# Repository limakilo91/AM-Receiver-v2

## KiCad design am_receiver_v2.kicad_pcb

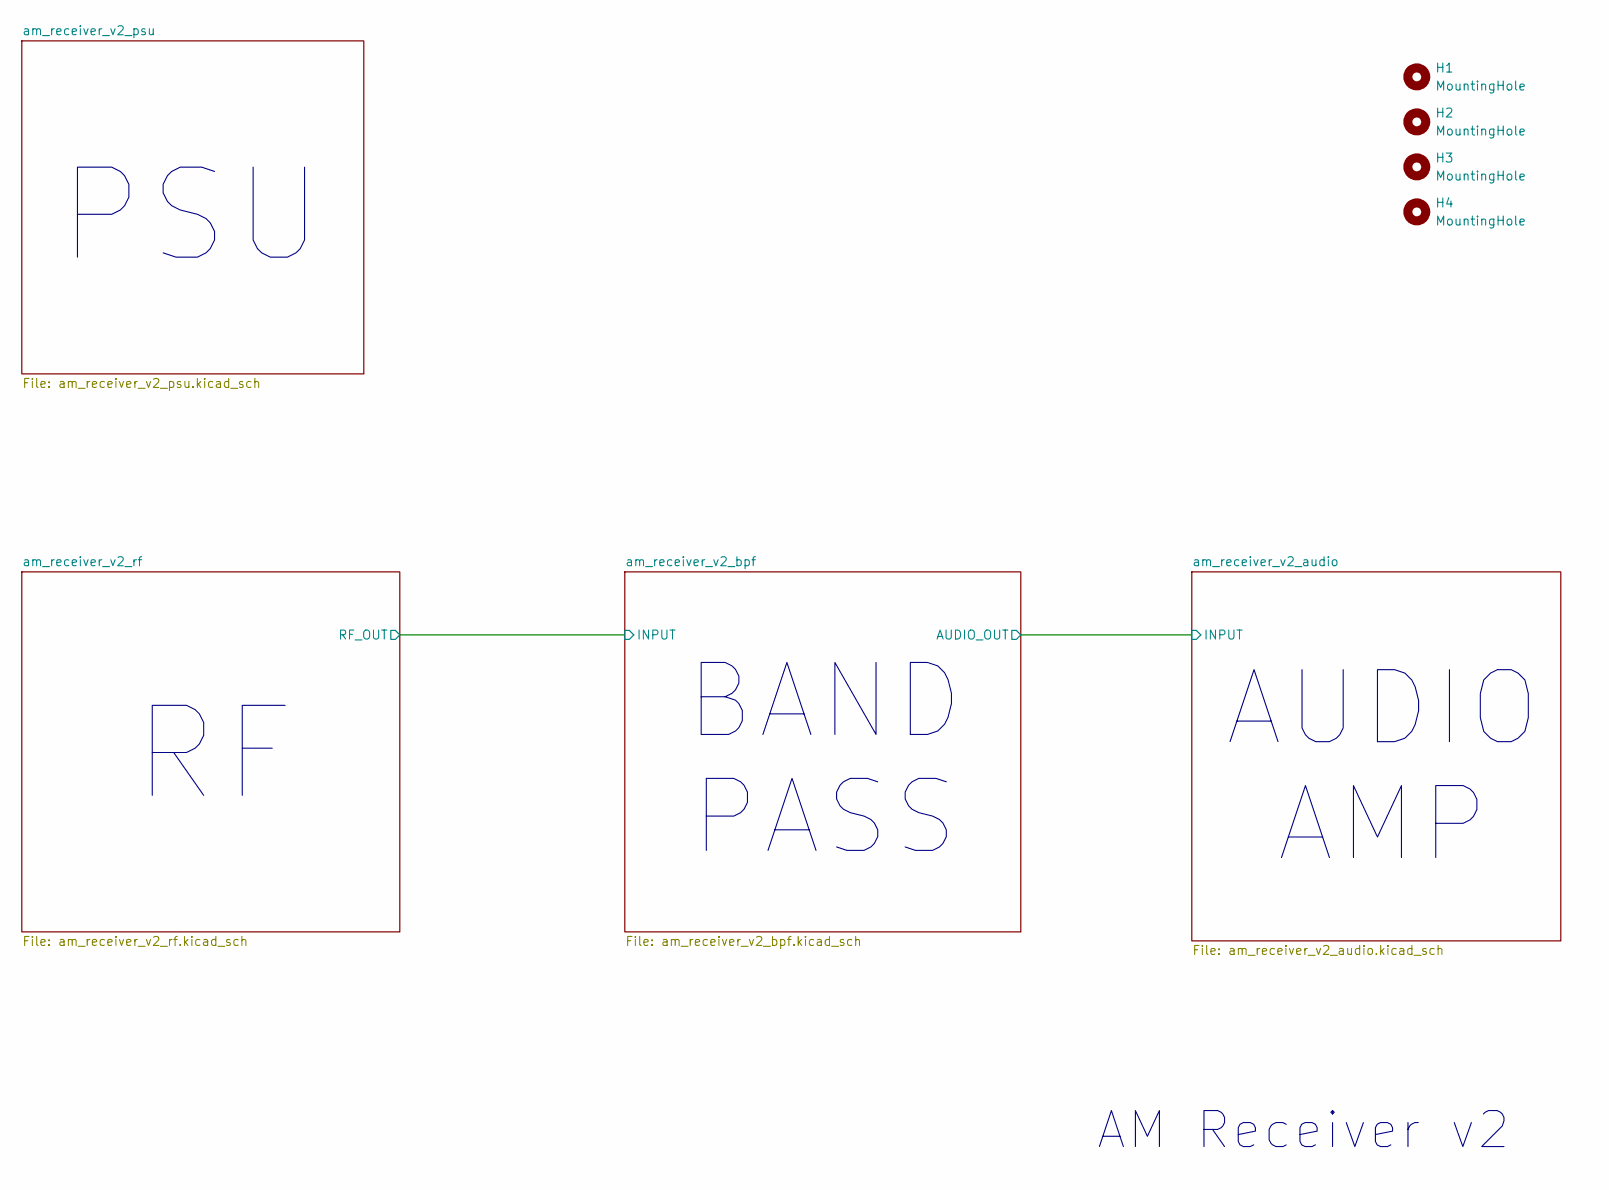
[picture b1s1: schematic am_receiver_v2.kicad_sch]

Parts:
H1, H2, H3, H4: MountingHole; MountingHole_3.2mm_M3_DIN965

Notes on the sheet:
PSU
AUDIO AMP
AM Receiver v2
BAND PASS

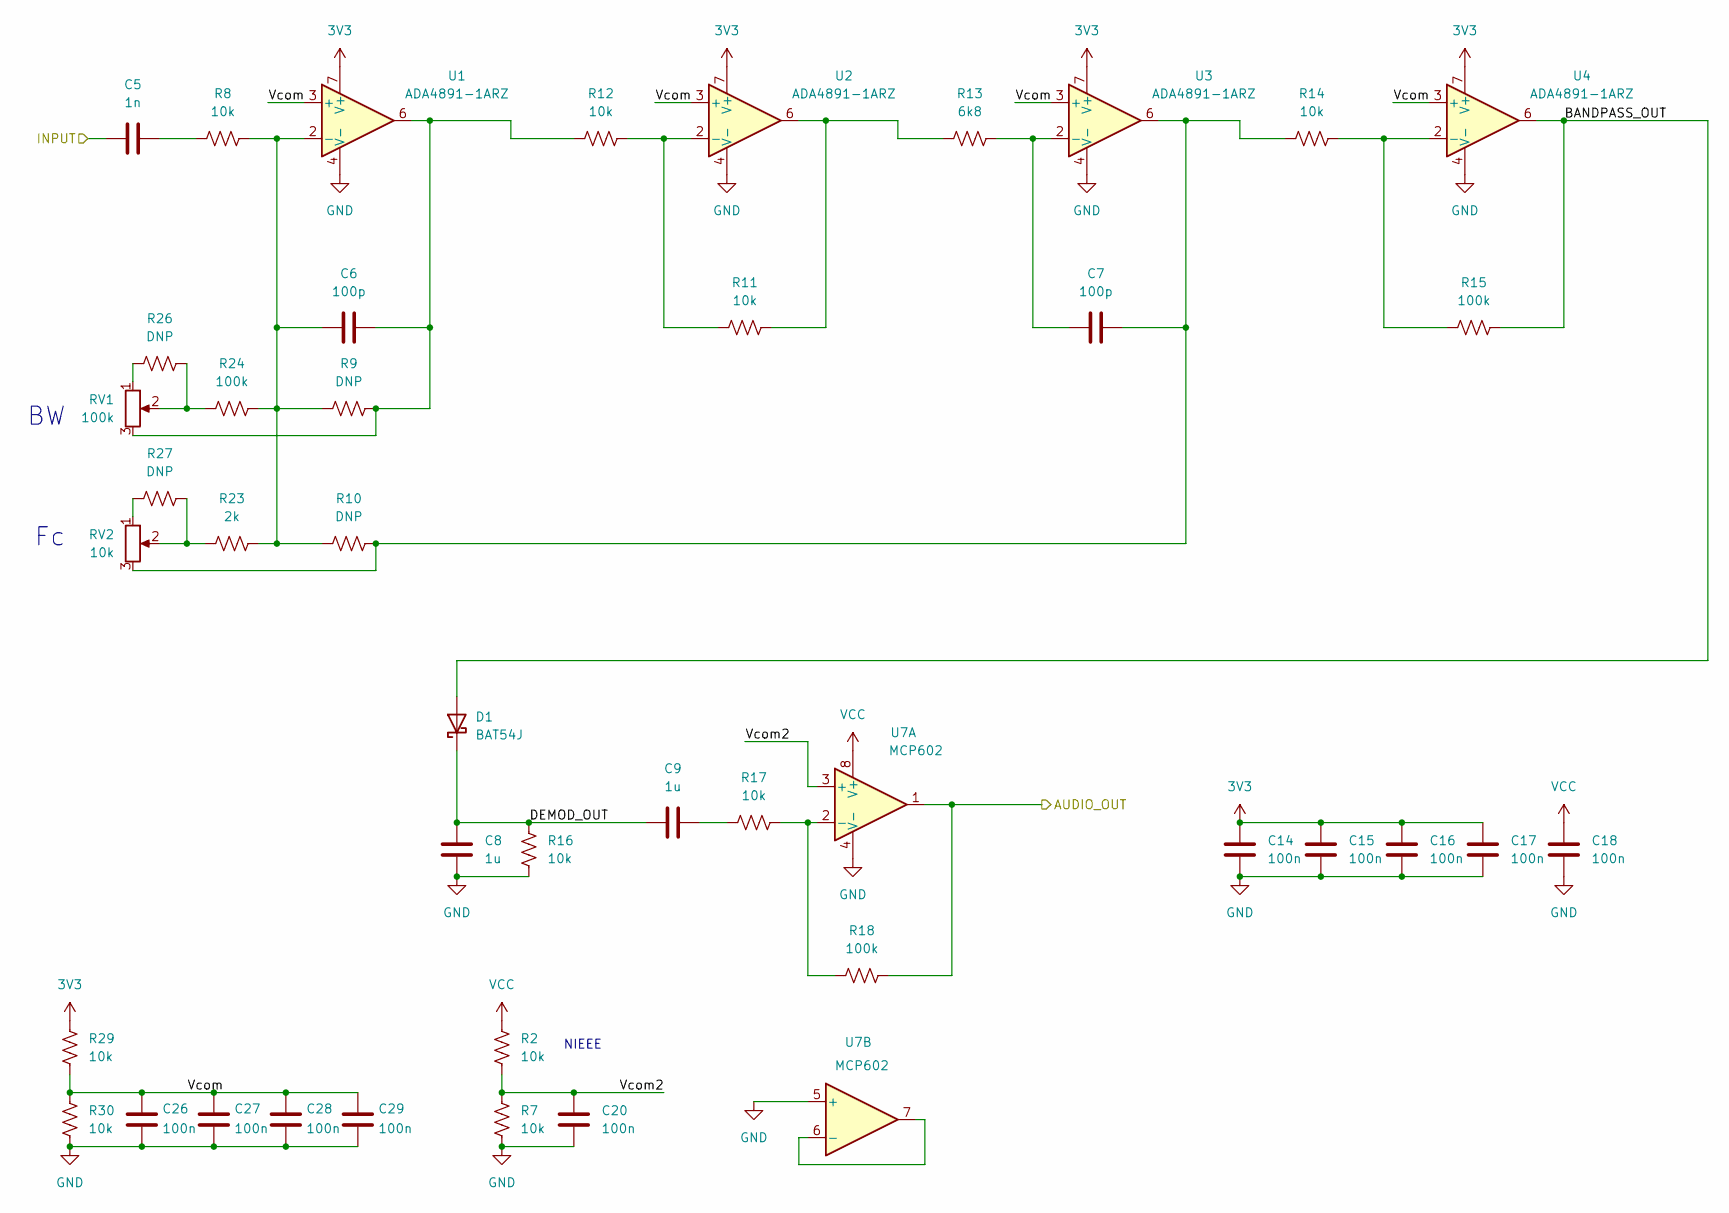
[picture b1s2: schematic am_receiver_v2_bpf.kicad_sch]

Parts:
C5: 1n; C_0603_1608Metric_Pad1.08x0.95mm_HandSolder
C6, C7: 100p; C_0603_1608Metric_Pad1.08x0.95mm_HandSolder
C8, C9: 1u; C_0603_1608Metric_Pad1.08x0.95mm_HandSolder
C14, C15, C16, C17, C18, C20, C26, C27, C28, C29: 100n; C_0603_1608Metric_Pad1.08x0.95mm_HandSolder
D1: BAT54J; D_SOD-323F
R2, R7, R8, R11, R12, R14, R16, R17, R29, R30: 10k; R_0603_1608Metric_Pad0.98x0.95mm_HandSolder
R9, R10, R26, R27: DNP; R_0603_1608Metric_Pad0.98x0.95mm_HandSolder
R13: 6k8; R_0603_1608Metric_Pad0.98x0.95mm_HandSolder
R15, R18, R24: 100k; R_0603_1608Metric_Pad0.98x0.95mm_HandSolder
R23: 2k; R_0603_1608Metric_Pad0.98x0.95mm_HandSolder
RV1: 100k; Potentiometer_Alps_RK163_Single_Horizontal
RV2: 10k; Potentiometer_Alps_RK163_Single_Horizontal
U1, U2, U3, U4: ADA4891-1ARZ; SOIC-8_3.9x4.9mm_P1.27mm
U7: MCP602; SOIC-8_3.9x4.9mm_P1.27mm

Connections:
3V3: C14.2, C15.2, C16.2, C17.2, R29.2, U1.7 (V+), U2.7 (V+), U3.7 (V+), U4.7 (V+); also elsewhere on the board
/am_receiver_v2_audio/INPUT: R18.2, U7.1; also elsewhere on the board
/am_receiver_v2_bpf/BANDPASS_OUT: D1.2 (A), R15.2, U4.6
/am_receiver_v2_bpf/DEMOD_OUT: C8.2, C9.1, D1.1 (K), R16.2
/am_receiver_v2_bpf/Vcom: C26.2, C27.2, C28.2, C29.2, R29.1, R30.2, U1.3 (+), U2.3 (+), U3.3 (+), U4.3 (+)
/am_receiver_v2_bpf/Vcom2: C20.2, R2.1, R7.2, U7.3 (+)
/am_receiver_v2_rf/RF_OUT: C5.1; also elsewhere on the board
GND: C8.1, C14.1, C15.1, C16.1, C17.1, C18.1, C20.1, C26.1, C27.1, C28.1, C29.1, R7.1, R16.1, R30.1, U1.4 (V-), U2.4 (V-), U3.4 (V-), U4.4 (V-), U7.4 (V-), U7.5 (+); also elsewhere on the board
unnamed: C5.2, R8.1
unnamed: C6.2, R9.2, R12.1, RV1.3, U1.6
unnamed: C7.2, R10.2, R14.1, RV2.3, U3.6
unnamed: C9.2, R17.1
unnamed: R11.2, R13.1, U2.6
unnamed: R23.1, R27.2, RV2.2
unnamed: R24.1, R26.2, RV1.2
unnamed: R26.1, RV1.1
unnamed: R27.1, RV2.1
unnamed: C6.1, R8.2, R9.1, R10.1, R23.2, R24.2, U1.2 (-)
unnamed: R11.1, R12.2, U2.2 (-)
unnamed: C7.1, R13.2, U3.2 (-)
unnamed: R14.2, R15.1, U4.2 (-)
unnamed: R17.2, R18.1, U7.2 (-)
unnamed: U7.6 (-), U7.7
VCC: C18.2, R2.2, U7.8 (V+); also elsewhere on the board

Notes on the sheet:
NIEEE

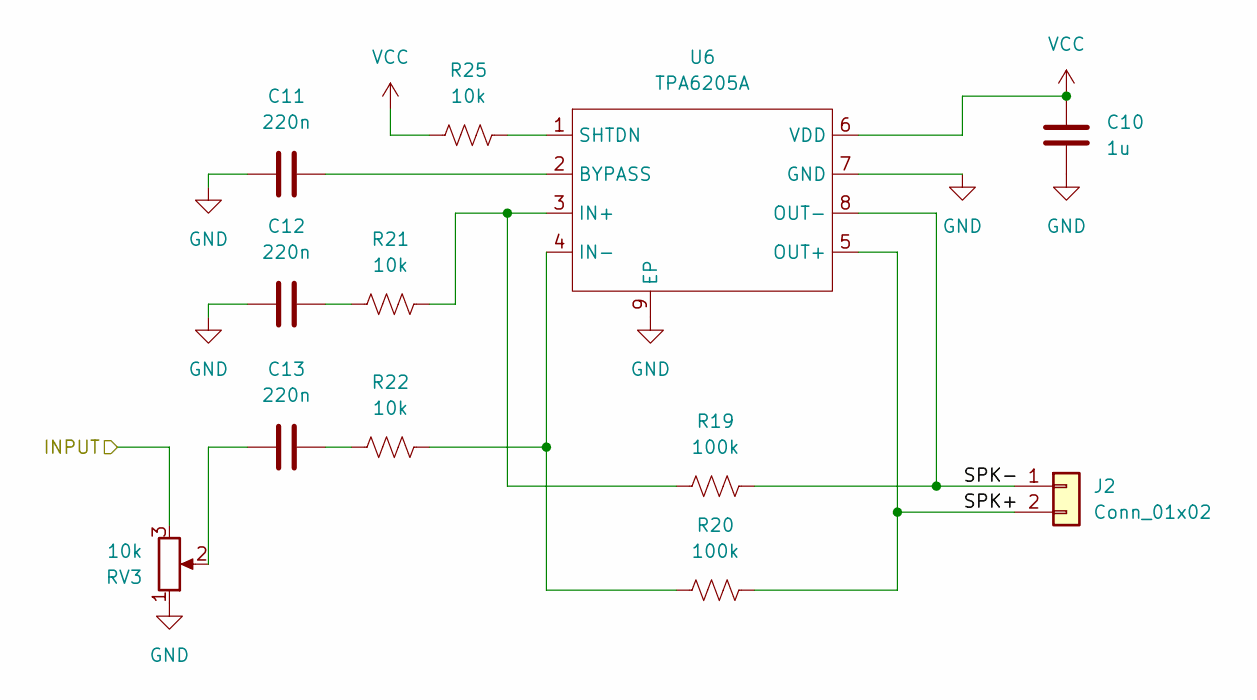
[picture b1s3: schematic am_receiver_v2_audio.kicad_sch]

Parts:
C10: 1u; C_0603_1608Metric_Pad1.08x0.95mm_HandSolder
C11, C12, C13: 220n; C_0603_1608Metric_Pad1.08x0.95mm_HandSolder
J2: Conn_01x02; PinSocket_1x02_P2.54mm_Vertical
R19, R20: 100k; R_0603_1608Metric_Pad0.98x0.95mm_HandSolder
R21, R22, R25: 10k; R_0603_1608Metric_Pad0.98x0.95mm_HandSolder
RV3: 10k; Potentiometer_Alps_RK163_Single_Horizontal
U6: TPA6205A; HVSSOP-8-1EP_3x3mm_P0.65mm_EP1.57x1.89mm

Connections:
/am_receiver_v2_audio/INPUT: RV3.3; also elsewhere on the board
/am_receiver_v2_audio/SPK+: J2.2, R20.2, U6.5 (OUT+)
/am_receiver_v2_audio/SPK-: J2.1, R19.2, U6.8 (OUT-)
GND: C10.2, C11.1, C12.1, RV3.1, U6.7 (GND), U6.9 (EP); also elsewhere on the board
unnamed: C12.2, R21.1
unnamed: C13.1, RV3.2
unnamed: C13.2, R22.1
unnamed: C11.2, U6.2 (BYPASS)
unnamed: R19.1, R21.2, U6.3 (IN+)
unnamed: R20.1, R22.2, U6.4 (IN-)
unnamed: R25.2, U6.1 (SHTDN)
VCC: C10.1, R25.1, U6.6 (VDD); also elsewhere on the board

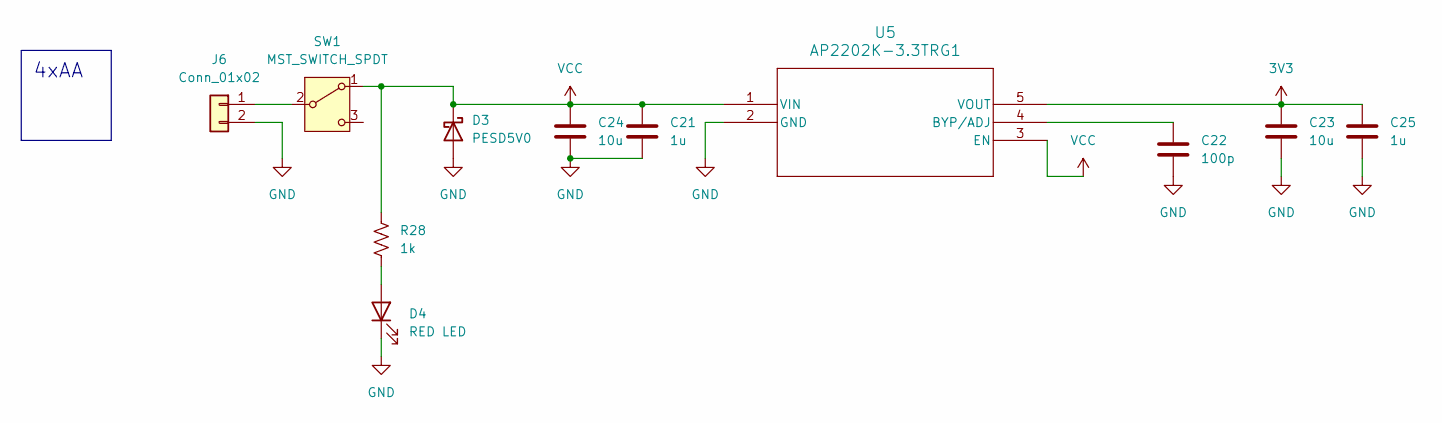
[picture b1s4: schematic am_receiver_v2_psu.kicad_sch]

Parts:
C21, C25: 1u; C_0603_1608Metric_Pad1.08x0.95mm_HandSolder
C22: 100p; C_0603_1608Metric_Pad1.08x0.95mm_HandSolder
C23, C24: 10u; C_0805_2012Metric_Pad1.18x1.45mm_HandSolder
D3: PESD5V0; D_SOD-323F
D4: RED LED; LED_0603_1608Metric_Pad1.05x0.95mm_HandSolder
J6: Conn_01x02; PinSocket_1x02_P2.54mm_Vertical
R28: 1k; R_0603_1608Metric_Pad0.98x0.95mm_HandSolder
SW1: MST_SWITCH_SPDT
U5: AP2202K-3.3TRG1; SOT-23-5_AP2202_DIO

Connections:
3V3: C23.1, C25.1, U5.5 (VOUT); also elsewhere on the board
GND: C21.2, C22.2, C23.2, C24.2, C25.2, D3.2 (A), D4.1 (K), J6.2, U5.2 (GND); also elsewhere on the board
unnamed: D4.2 (A), R28.2
unnamed: J6.1, SW1.2 (B)
unnamed: C22.1, U5.4 (BYP/ADJ)
VCC: C21.1, C24.1, D3.1 (K), R28.1, SW1.1 (A), U5.1 (VIN), U5.3 (EN); also elsewhere on the board

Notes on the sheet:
4xAA

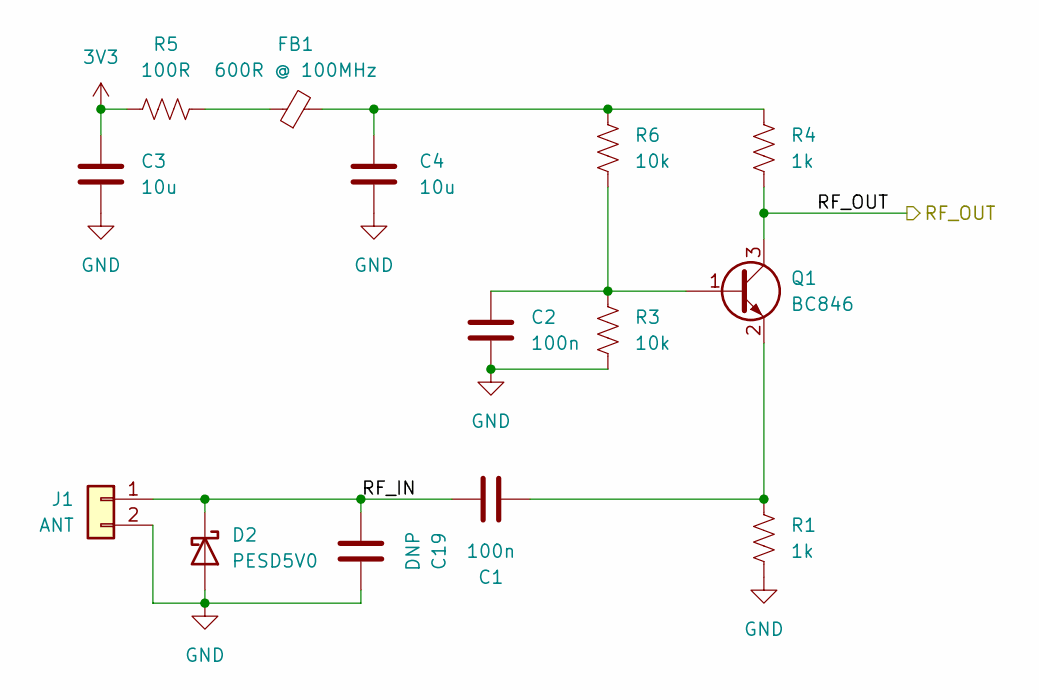
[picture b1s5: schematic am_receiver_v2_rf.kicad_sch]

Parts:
C1, C2: 100n; C_0603_1608Metric_Pad1.08x0.95mm_HandSolder
C3, C4: 10u; C_0805_2012Metric_Pad1.18x1.45mm_HandSolder
C19: DNP; C_0603_1608Metric_Pad1.08x0.95mm_HandSolder
D2: PESD5V0; D_SOD-323F
FB1: 600R @ 100MHz; L_0805_2012Metric_Pad1.05x1.20mm_HandSolder
J1: ANT; PinSocket_1x02_P2.54mm_Vertical
Q1: BC846; SOT-23
R1, R4: 1k; R_0603_1608Metric_Pad0.98x0.95mm_HandSolder
R3, R6: 10k; R_0603_1608Metric_Pad0.98x0.95mm_HandSolder
R5: 100R; R_0603_1608Metric_Pad0.98x0.95mm_HandSolder

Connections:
3V3: C3.1, R5.1; also elsewhere on the board
/am_receiver_v2_rf/RF_IN: C1.1, C19.2, D2.1 (K), J1.1
/am_receiver_v2_rf/RF_OUT: Q1.3 (C), R4.2; also elsewhere on the board
GND: C2.2, C3.2, C4.2, C19.1, D2.2 (A), J1.2, R1.2, R3.2; also elsewhere on the board
unnamed: C4.1, FB1.2, R4.1, R6.1
unnamed: FB1.1, R5.2
unnamed: C2.1, Q1.1 (B), R3.1, R6.2
unnamed: C1.2, Q1.2 (E), R1.1

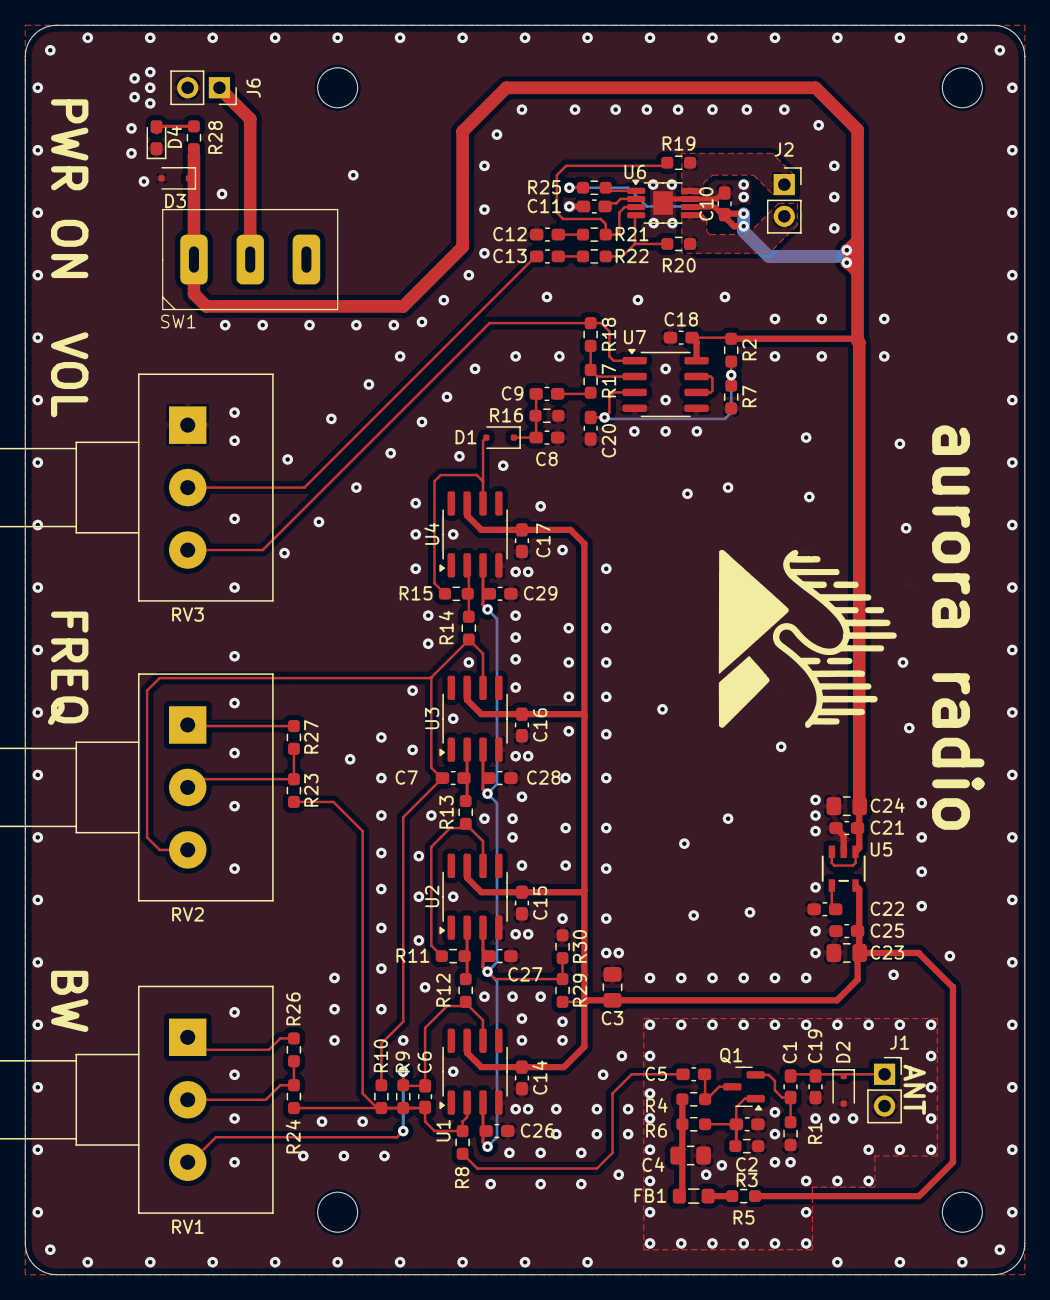
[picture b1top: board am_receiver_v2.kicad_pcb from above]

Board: 2 copper layers, 80.0 x 100.0 mm, 83 parts (0 on the bottom side), 41 nets.

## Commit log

2025-04-16 init commit
2025-04-16 added description
2025-04-16 added sch print
